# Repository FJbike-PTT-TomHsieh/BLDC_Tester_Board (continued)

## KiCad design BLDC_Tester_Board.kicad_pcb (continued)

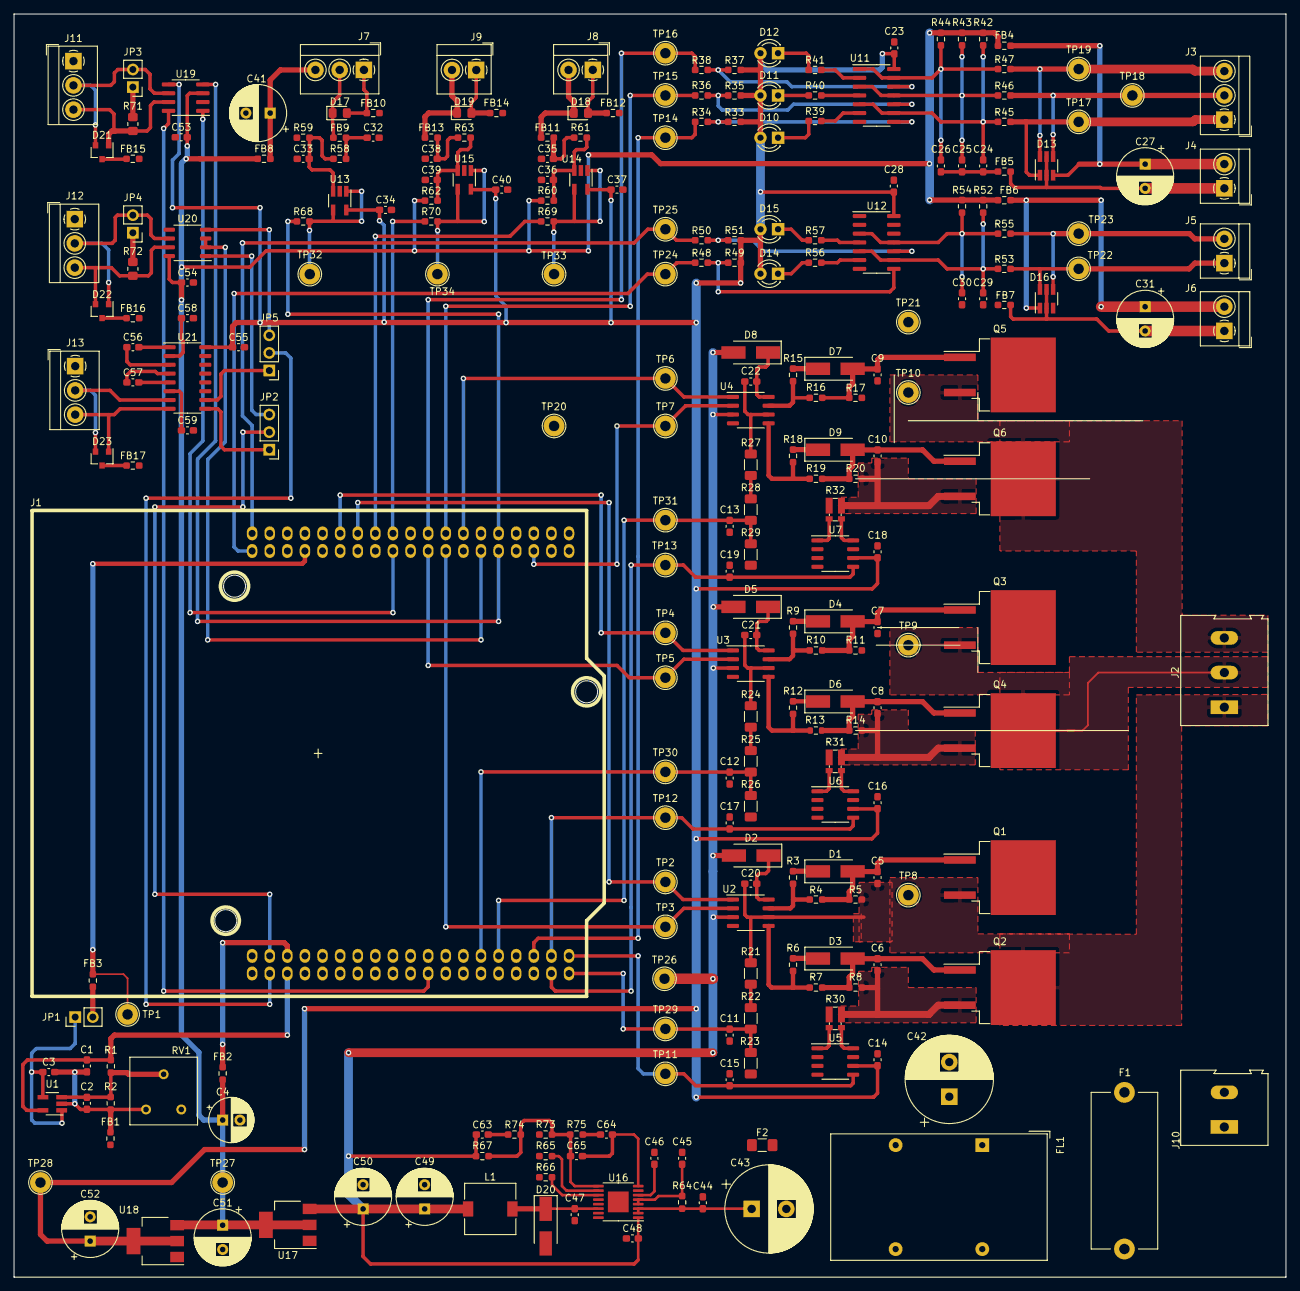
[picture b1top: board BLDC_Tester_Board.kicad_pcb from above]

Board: 2 copper layers, 183.5 x 182.2 mm, 258 parts (0 on the bottom side), 154 nets.

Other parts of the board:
C53, C54, C55, C56, C57, C58, C59: 100nF; C_0603_1608Metric_Pad1.08x0.95mm_HandSolder
D21: PESD2CAN; SOT-23
D22: D_TVS_x2_AAC; SOT-23
D23: SM712_SOT23; SOT-23
FB15, FB16, FB17: Ferrite_Bead; R_0603_1608Metric_Pad0.98x0.95mm_HandSolder
J11, J12, J13: Screw_Terminal_01x03; TerminalBlock_4Ucon_1x03_P3.50mm_Horizontal
JP2, JP5: Jumper_3_Bridged12; PinHeader_1x03_P2.54mm_Vertical
JP3, JP4: Jumper_NC_Small; PinHeader_1x02_P2.54mm_Vertical
R71: 120; R_0805_2012Metric_Pad1.20x1.40mm_HandSolder
R72: 220; R_0805_2012Metric_Pad1.20x1.40mm_HandSolder
U19: MCP2558FD-xSN; SOIC-8_3.9x4.9mm_P1.27mm
U20: MAX485E; SOP-8_3.9x4.9mm_P1.27mm
U21: MAX3232; SO-16_3.9x9.9mm_P1.27mm

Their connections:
/DC to DC/3V3: C55.1, U19.5, U21.16; also elsewhere on the board
/DC to DC/5V: C53.1, C54.1, U19.3, U20.8; also elsewhere on the board
/RS485 & CANFD interface/CAN+: D21.1, J11.3, R71.2, U19.7
/RS485 & CANFD interface/CAN-: D21.2, J11.2, JP3.2, U19.6
/RS485 & CANFD interface/CAN_GND: D21.3, FB15.1, J11.1
/RS485 & CANFD interface/L232_RX: JP2.1, U21.9
/RS485 & CANFD interface/L232_TX: JP5.1, U21.10
/RS485 & CANFD interface/L485_RX: JP2.3, U20.1
/RS485 & CANFD interface/L485_TX: JP5.3, U20.4
/RS485 & CANFD interface/RS232_GND: D23.3, FB17.1, J13.1
/RS485 & CANFD interface/RS232_RX: D23.1, J13.3, U21.8
/RS485 & CANFD interface/RS232_TX: D23.2, J13.2, U21.7
/RS485 & CANFD interface/RS485+: D22.2, J12.3, R72.2, U20.7
/RS485 & CANFD interface/RS485-: D22.1, J12.2, JP4.2, U20.6
/RS485 & CANFD interface/RS485_GND: D22.3, FB16.1, J12.1
GND: C53.2, C54.2, C55.2, C58.1, C59.1, FB15.2, FB16.2, FB17.2, U19.2, U20.5, U21.15; also elsewhere on the board
unnamed: C56.1, U21.1
unnamed: C56.2, U21.3
unnamed: C57.1, U21.4
unnamed: C57.2, U21.5
unnamed: C58.2, U21.2
unnamed: C59.2, U21.6
unnamed: JP3.1, R71.1
unnamed: JP4.1, R72.1
PB4_UART5_DE: U20.2, U20.3; also elsewhere on the board
PB5_CAN2_RX: U19.4; also elsewhere on the board
PB6_CAN2_TX: U19.1; also elsewhere on the board
PB7: U19.8; also elsewhere on the board
PC12_UART5_TX: JP5.2; also elsewhere on the board
PD2_UART5_RX: JP2.2; also elsewhere on the board

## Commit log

2021-04-22 First
2021-04-23 Update_04232021
2021-04-26 Update_0426_2021
2021-04-27 main
2021-04-28 0428_2021_Update
2021-04-29 0429_2021_Update
2021-05-03 0503_2021_Update
